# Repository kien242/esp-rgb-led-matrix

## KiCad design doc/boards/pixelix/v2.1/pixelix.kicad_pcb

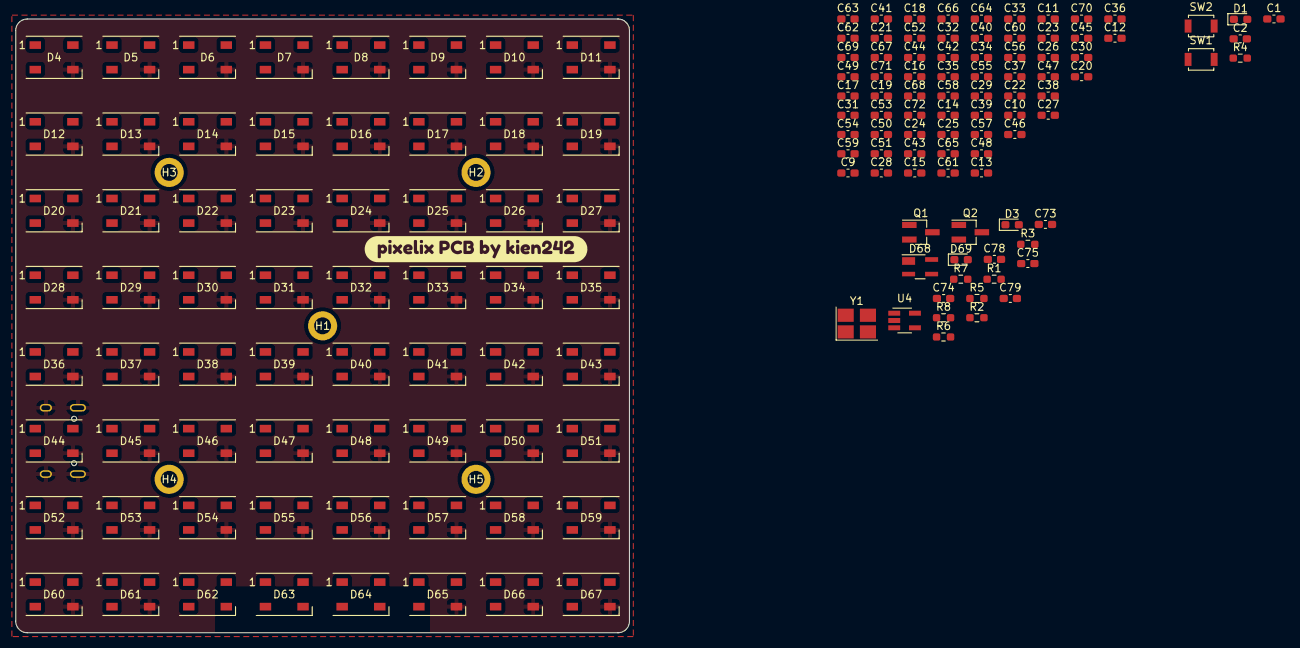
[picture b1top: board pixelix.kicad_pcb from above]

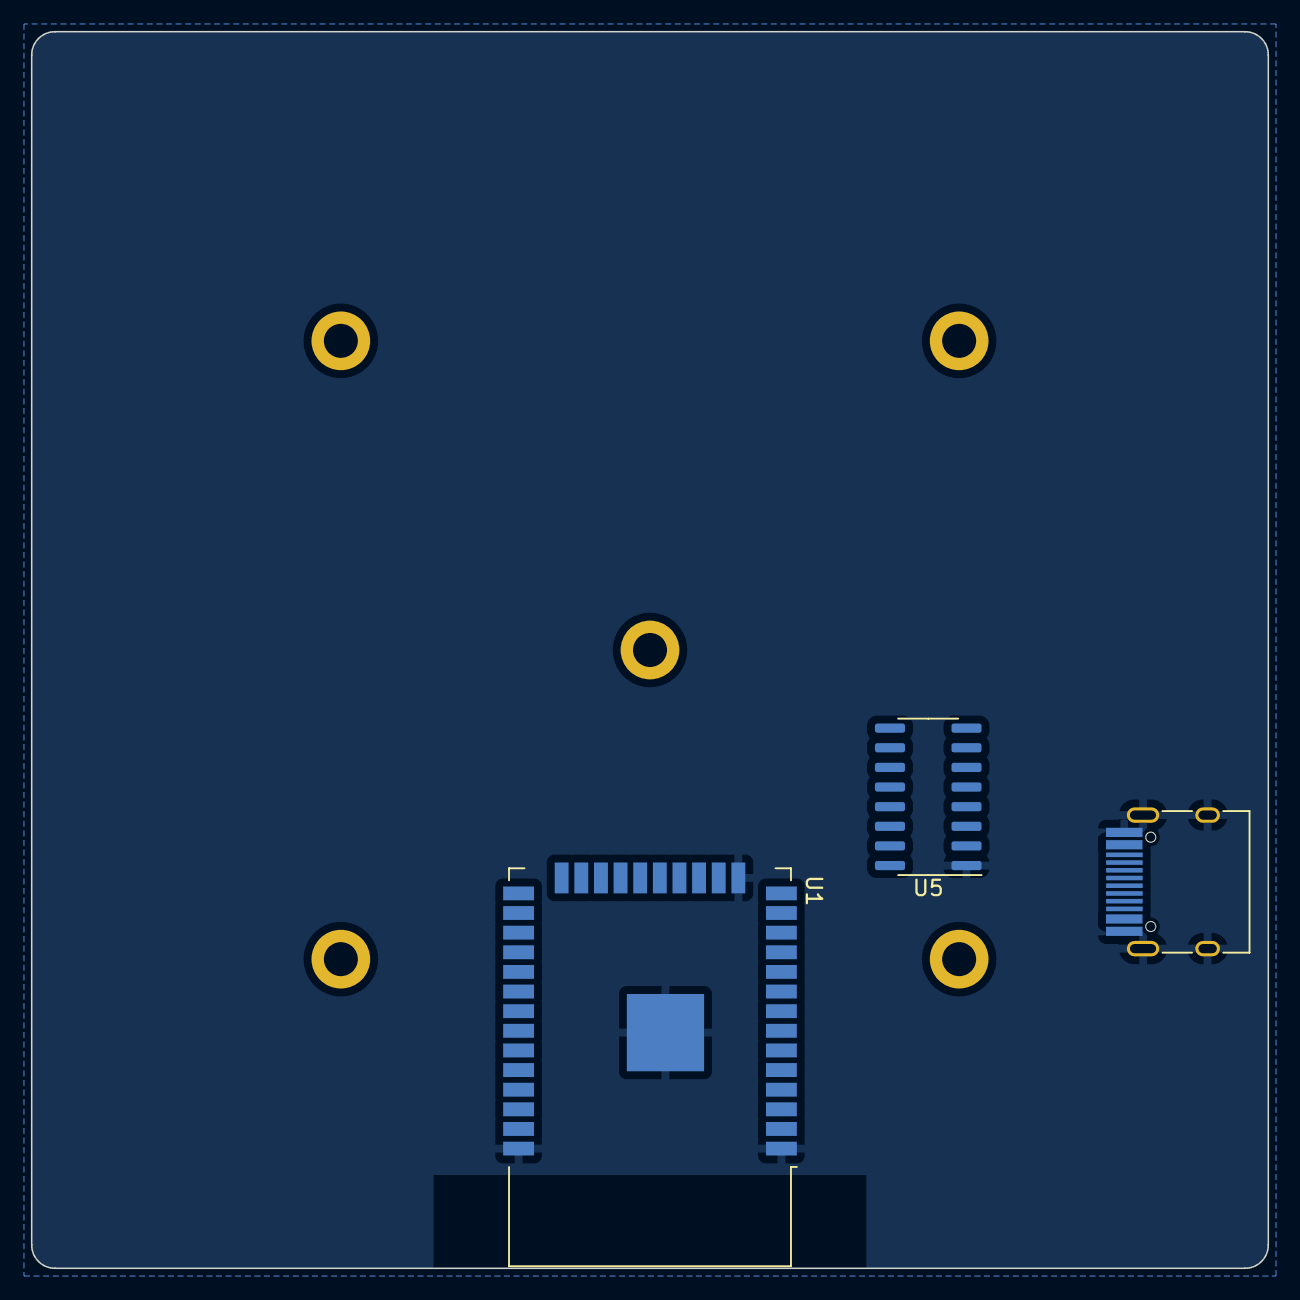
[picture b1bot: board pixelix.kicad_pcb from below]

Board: 2 copper layers, 80.0 x 80.0 mm, 162 parts (3 on the bottom side), 85 nets, no tracks yet.

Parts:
C1, C2: 1nf; C_0603_1608Metric_Pad1.08x0.95mm_HandSolder
C9, C10, C11, C12, C13, C14, C15, C16, C17, C18, C19, C20, C21, C22, C23, C24, C25, C26, C27, C28, C29, C30, C31, C32, C33, C34, C35, C36, C37, C38, C39, C40, C41, C42, C43, C44, C45, C46, C47, C48, C49, C50, C51, C52, C53, C54, C55, C56, C57, C58, C59, C60, C61, C62, C63, C64, C65, C66, C67, C68, C69, C70, C71, C72: 104; C_0603_1608Metric_Pad1.08x0.95mm_HandSolder
C73, C74: 10uF; C_0603_1608Metric_Pad1.08x0.95mm_HandSolder
C75: 100nF; C_0603_1608Metric_Pad1.08x0.95mm_HandSolder
C78, C79: 9pF; C_0603_1608Metric_Pad1.08x0.95mm_HandSolder
D1, D69: GREEN; LED_0603_1608Metric_Pad1.05x0.95mm_HandSolder
D3: RED; LED_0603_1608Metric_Pad1.05x0.95mm_HandSolder
D4, D5, D6, D7, D8, D9, D10, D11, D12, D13, D14, D15, D16, D17, D18, D19, D20, D21, D22, D23, D24, D25, D26, D27, D28, D29, D30, D31, D32, D33, D34, D35, D36, D37, D38, D39, D40, D41, D42, D43, D44, D45, D46, D47, D48, D49, D50, D51, D52, D53, D54, D55, D56, D57, D58, D59, D60, D61, D62, D63, D64, D65, D66, D67: LED_WS2812B_PLCC4_5.0x5.0mm_P3.2mm
D68: PRTR5V0U2X; SOT-143_Handsoldering
H1, H2, H3, H4, H5: M2; MountingHole_2.2mm_M2_DIN965_Pad
J1: USB-C-16pin-hight-v2
Q1, Q2: MMBT3904; SOT-23_Handsoldering
R1, R2, R3, R4: 10K; R_0603_1608Metric_Pad0.98x0.95mm_HandSolder
R5, R6: 100; R_0603_1608Metric_Pad0.98x0.95mm_HandSolder
R7, R8: 1K; R_0603_1608Metric_Pad0.98x0.95mm_HandSolder
SW1, SW2: SWITCH_SPST; SW_SPST_B3U-1000P
U1: ESP32-WROOM; ESP32-WROOM-32
U4: AP2127K-3.3; SOT-23-5_HandSoldering
U5: CH340G; SOIC-16_3.9x9.9mm_P1.27mm
Y1: 32.768kHz; Crystal_SMD_SeikoEpson_TSX3225-4Pin_3.2x2.5mm_HandSoldering
kibuzzard-62F63F5E: G***; kibuzzard-62F63F5E

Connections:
+3V3: C74.1, C75.2, R1.2, R7.1, R8.1, U1.2 (3V3), U4.5 (VOUT), U5.4 (V3), U5.16 (VCC)
+5V: C73.1, J1.A4 (VBUS), J1.A9 (VBUS), J1.B4 (VBUS), J1.B9 (VBUS), U4.1 (VIN), U4.3 (EN)
D+: D68.2 (I/O1), J1.A7 (D-), J1.B7 (D-), U5.5 (UD+)
D-: D68.3 (I/O2), J1.A6 (D+), J1.B6 (D+), U5.6 (UD-)
DTR: Q2.2 (E), R2.1, U5.13 (~DTR)
EN: C1.1, Q1.3 (C), R1.1, SW1.1, U1.3 (EN)
GND: C1.2, C2.2, C9.2, C10.2, C11.2, C12.2, C13.2, C14.2, C15.2, C16.2, C17.2, C18.2, C19.2, C20.2, C21.2, C22.2, C23.2, C24.2, C25.2, C26.2, C27.2, C28.2, C29.2, C30.2, C31.2, C32.2, C33.2, C34.2, C35.2, C36.2, C37.2, C38.2, C39.2, C40.2, C41.2, C42.2, C43.2, C44.2, C45.2, C46.2, C47.2, C48.2, C49.2, C50.2, C51.2, C52.2, C53.2, C54.2, C55.2, C56.2, C57.2, C58.2, C59.2, C60.2, C61.2, C62.2, C63.2, C64.2, C65.2, C66.2, C67.2, C68.2, C69.2, C70.2, C71.2, C72.2, C73.2, C74.2, C75.1, C78.2, C79.2, D1.1 (K), D4.3 (VSS), D5.3 (VSS), D6.3 (VSS), D7.3 (VSS), D8.3 (VSS), D9.3 (VSS), D10.3 (VSS), D11.3 (VSS), D12.3 (VSS), D13.3 (VSS), D14.3 (VSS), D15.3 (VSS), D16.3 (VSS), D17.3 (VSS), D18.3 (VSS), D19.3 (VSS), D20.3 (VSS), D21.3 (VSS), D22.3 (VSS), D23.3 (VSS), D24.3 (VSS), D25.3 (VSS), D26.3 (VSS), D27.3 (VSS), D28.3 (VSS), D29.3 (VSS), D30.3 (VSS), D31.3 (VSS), D32.3 (VSS), D33.3 (VSS), D34.3 (VSS), D35.3 (VSS), D36.3 (VSS), D37.3 (VSS), D38.3 (VSS), D39.3 (VSS), D40.3 (VSS), D41.3 (VSS), D42.3 (VSS), D43.3 (VSS), D44.3 (VSS), D45.3 (VSS), D46.3 (VSS), D47.3 (VSS), D48.3 (VSS), D49.3 (VSS), D50.3 (VSS), D51.3 (VSS), D52.3 (VSS), D53.3 (VSS), D54.3 (VSS), D55.3 (VSS), D56.3 (VSS), D57.3 (VSS), D58.3 (VSS), D59.3 (VSS), D60.3 (VSS), D61.3 (VSS), D62.3 (VSS), D63.3 (VSS), D64.3 (VSS), D65.3 (VSS), D66.3 (VSS), D67.3 (VSS), D68.1 (GND), J1.A1 (GND), J1.A12 (GND), J1.B1 (GND), J1.B12 (GND), J1.S1 (SHIELD), SW1.2, SW2.2, U1.1 (GND), U1.15 (GND), U1.38 (GND), U1.39 (GND-PAD), U4.2 (GND), U5.1 (GND), Y1.2, Y1.4
IO0(boot): C2.1, Q2.3 (C), SW2.1, U1.25 (IO0)
IO5: R4.1, U1.29 (IO5)
unnamed: D1.2 (A), R4.2
unnamed: D3.2 (A), R8.2
unnamed: D4.2 (DOUT), D12.4 (DIN)
unnamed: D5.2 (DOUT), D13.4 (DIN)
unnamed: D5.1 (VDD), D13.1 (VDD), D21.1 (VDD), D29.1 (VDD), D37.1 (VDD), D45.1 (VDD), D53.1 (VDD), D61.1 (VDD)
unnamed: D6.2 (DOUT), D14.4 (DIN)
unnamed: D7.2 (DOUT), D15.4 (DIN)
unnamed: D8.2 (DOUT), D16.4 (DIN)
unnamed: D9.2 (DOUT), D17.4 (DIN)
unnamed: D10.2 (DOUT), D18.4 (DIN)
unnamed: D11.2 (DOUT), D19.4 (DIN)
unnamed: D11.1 (VDD), D19.1 (VDD), D27.1 (VDD), D35.1 (VDD), D43.1 (VDD), D51.1 (VDD), D59.1 (VDD), D67.1 (VDD)
unnamed: D12.2 (DOUT), D20.4 (DIN)
unnamed: D13.2 (DOUT), D21.4 (DIN)
unnamed: D14.2 (DOUT), D22.4 (DIN)
unnamed: D15.2 (DOUT), D23.4 (DIN)
unnamed: D16.2 (DOUT), D24.4 (DIN)
unnamed: D17.2 (DOUT), D25.4 (DIN)
unnamed: D9.1 (VDD), D17.1 (VDD), D25.1 (VDD), D33.1 (VDD), D41.1 (VDD), D49.1 (VDD), D57.1 (VDD), D65.1 (VDD)
unnamed: D18.2 (DOUT), D26.4 (DIN)
unnamed: D19.2 (DOUT), D27.4 (DIN)
unnamed: D20.2 (DOUT), D28.4 (DIN)
unnamed: D21.2 (DOUT), D29.4 (DIN)
unnamed: D22.2 (DOUT), D30.4 (DIN)
unnamed: D6.1 (VDD), D14.1 (VDD), D22.1 (VDD), D30.1 (VDD), D38.1 (VDD), D46.1 (VDD), D54.1 (VDD), D62.1 (VDD)
unnamed: D23.2 (DOUT), D31.4 (DIN)
unnamed: D7.1 (VDD), D15.1 (VDD), D23.1 (VDD), D31.1 (VDD), D39.1 (VDD), D47.1 (VDD), D55.1 (VDD), D63.1 (VDD)
unnamed: D24.2 (DOUT), D32.4 (DIN)
unnamed: D25.2 (DOUT), D33.4 (DIN)
unnamed: D26.2 (DOUT), D34.4 (DIN)
unnamed: D10.1 (VDD), D18.1 (VDD), D26.1 (VDD), D34.1 (VDD), D42.1 (VDD), D50.1 (VDD), D58.1 (VDD), D66.1 (VDD)
unnamed: D27.2 (DOUT), D35.4 (DIN)
unnamed: D28.2 (DOUT), D36.4 (DIN)
unnamed: D29.2 (DOUT), D37.4 (DIN)
unnamed: D30.2 (DOUT), D38.4 (DIN)
unnamed: D31.2 (DOUT), D39.4 (DIN)
unnamed: D32.2 (DOUT), D40.4 (DIN)
unnamed: D8.1 (VDD), D16.1 (VDD), D24.1 (VDD), D32.1 (VDD), D40.1 (VDD), D48.1 (VDD), D56.1 (VDD), D64.1 (VDD)
unnamed: D33.2 (DOUT), D41.4 (DIN)
unnamed: D34.2 (DOUT), D42.4 (DIN)
unnamed: D35.2 (DOUT), D43.4 (DIN)
unnamed: D36.2 (DOUT), D44.4 (DIN)
unnamed: D37.2 (DOUT), D45.4 (DIN)
unnamed: D38.2 (DOUT), D46.4 (DIN)
unnamed: D39.2 (DOUT), D47.4 (DIN)
unnamed: D40.2 (DOUT), D48.4 (DIN)
unnamed: D41.2 (DOUT), D49.4 (DIN)
unnamed: D42.2 (DOUT), D50.4 (DIN)
unnamed: D43.2 (DOUT), D51.4 (DIN)
unnamed: D45.2 (DOUT), D53.4 (DIN)
unnamed: D46.2 (DOUT), D54.4 (DIN)
unnamed: D47.2 (DOUT), D55.4 (DIN)
unnamed: D48.2 (DOUT), D56.4 (DIN)
unnamed: D49.2 (DOUT), D57.4 (DIN)
unnamed: D50.2 (DOUT), D58.4 (DIN)
unnamed: D51.2 (DOUT), D59.4 (DIN)
unnamed: D44.2 (DOUT), D52.4 (DIN)
unnamed: D52.2 (DOUT), D60.4 (DIN)
unnamed: D53.2 (DOUT), D61.4 (DIN)
unnamed: D54.2 (DOUT), D62.4 (DIN)
unnamed: D55.2 (DOUT), D63.4 (DIN)
unnamed: D56.2 (DOUT), D64.4 (DIN)
unnamed: D57.2 (DOUT), D65.4 (DIN)
unnamed: D58.2 (DOUT), D66.4 (DIN)
unnamed: D59.2 (DOUT), D67.4 (DIN)
unnamed: C9.1, C10.1, C11.1, C12.1, C13.1, C14.1, D4.1 (VDD), D12.1 (VDD), D20.1 (VDD), D28.1 (VDD), D36.1 (VDD), D44.1 (VDD), D52.1 (VDD), D60.1 (VDD)
unnamed: D69.2 (A), R7.2
unnamed: Q1.1 (B), R2.2
unnamed: Q2.1 (B), R3.2
unnamed: R6.2, U5.3 (RXD)
unnamed: R5.2, U5.2 (TXD)
unnamed: C78.1, U5.7 (XI), Y1.1
unnamed: C79.1, U5.8 (XO), Y1.3
RTS: Q1.2 (E), R3.1, U5.14 (~RTS)
RXDtoTXD0: D69.1 (K), R6.1, U1.35 (TXD0)
TXDtoRXD0: D3.1 (K), R5.1, U1.34 (RXD0)

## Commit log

2022-08-12 add PCB pixelix
2022-08-12 Update file kicad
